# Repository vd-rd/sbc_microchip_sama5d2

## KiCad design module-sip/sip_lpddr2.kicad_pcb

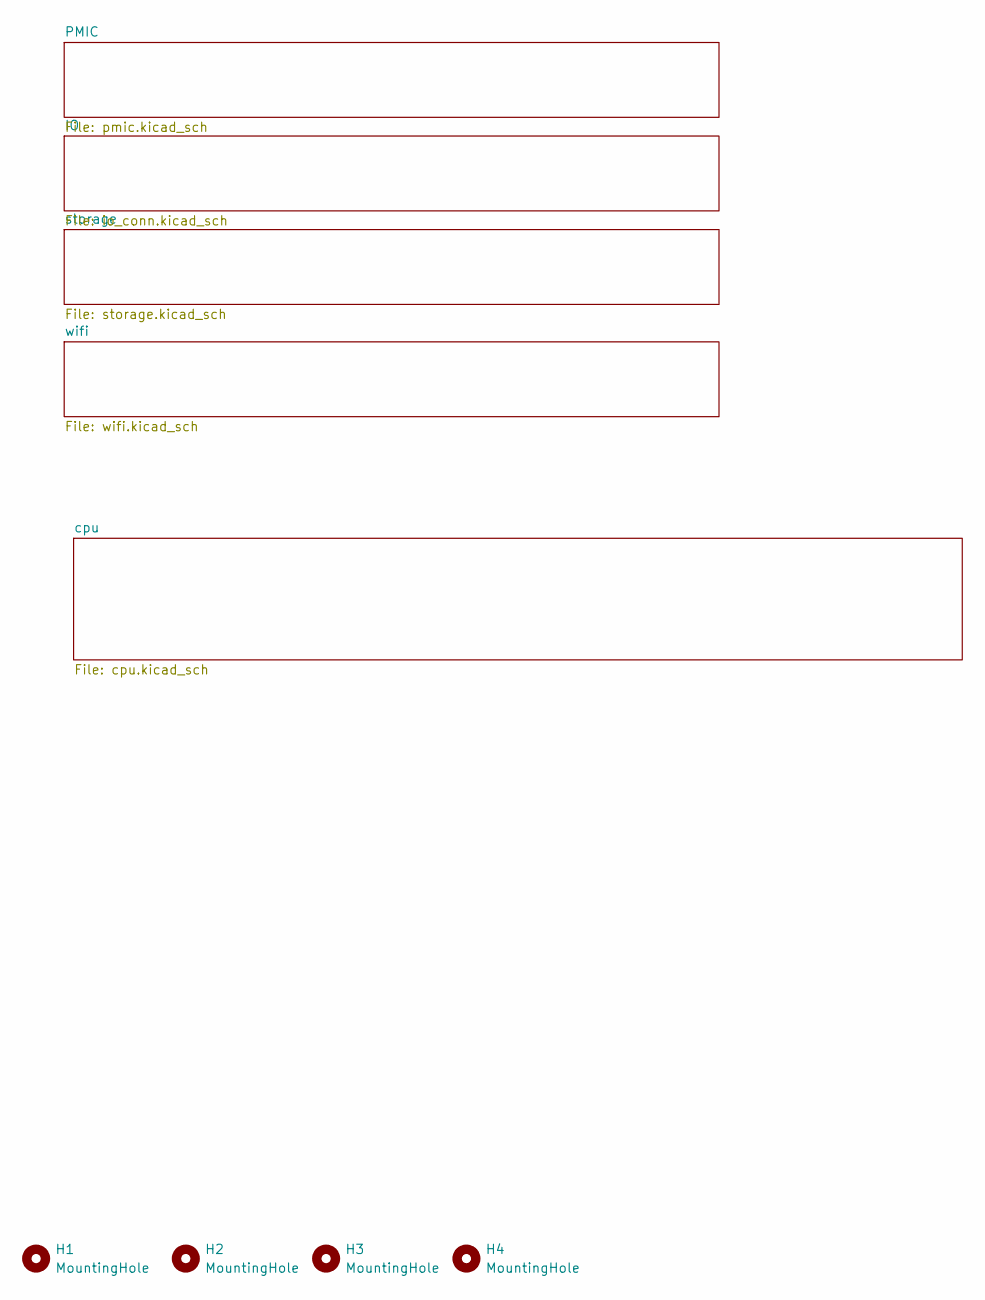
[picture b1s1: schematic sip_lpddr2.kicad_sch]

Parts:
H1, H2, H3, H4: MountingHole; MountingHole_2.7mm_M2.5

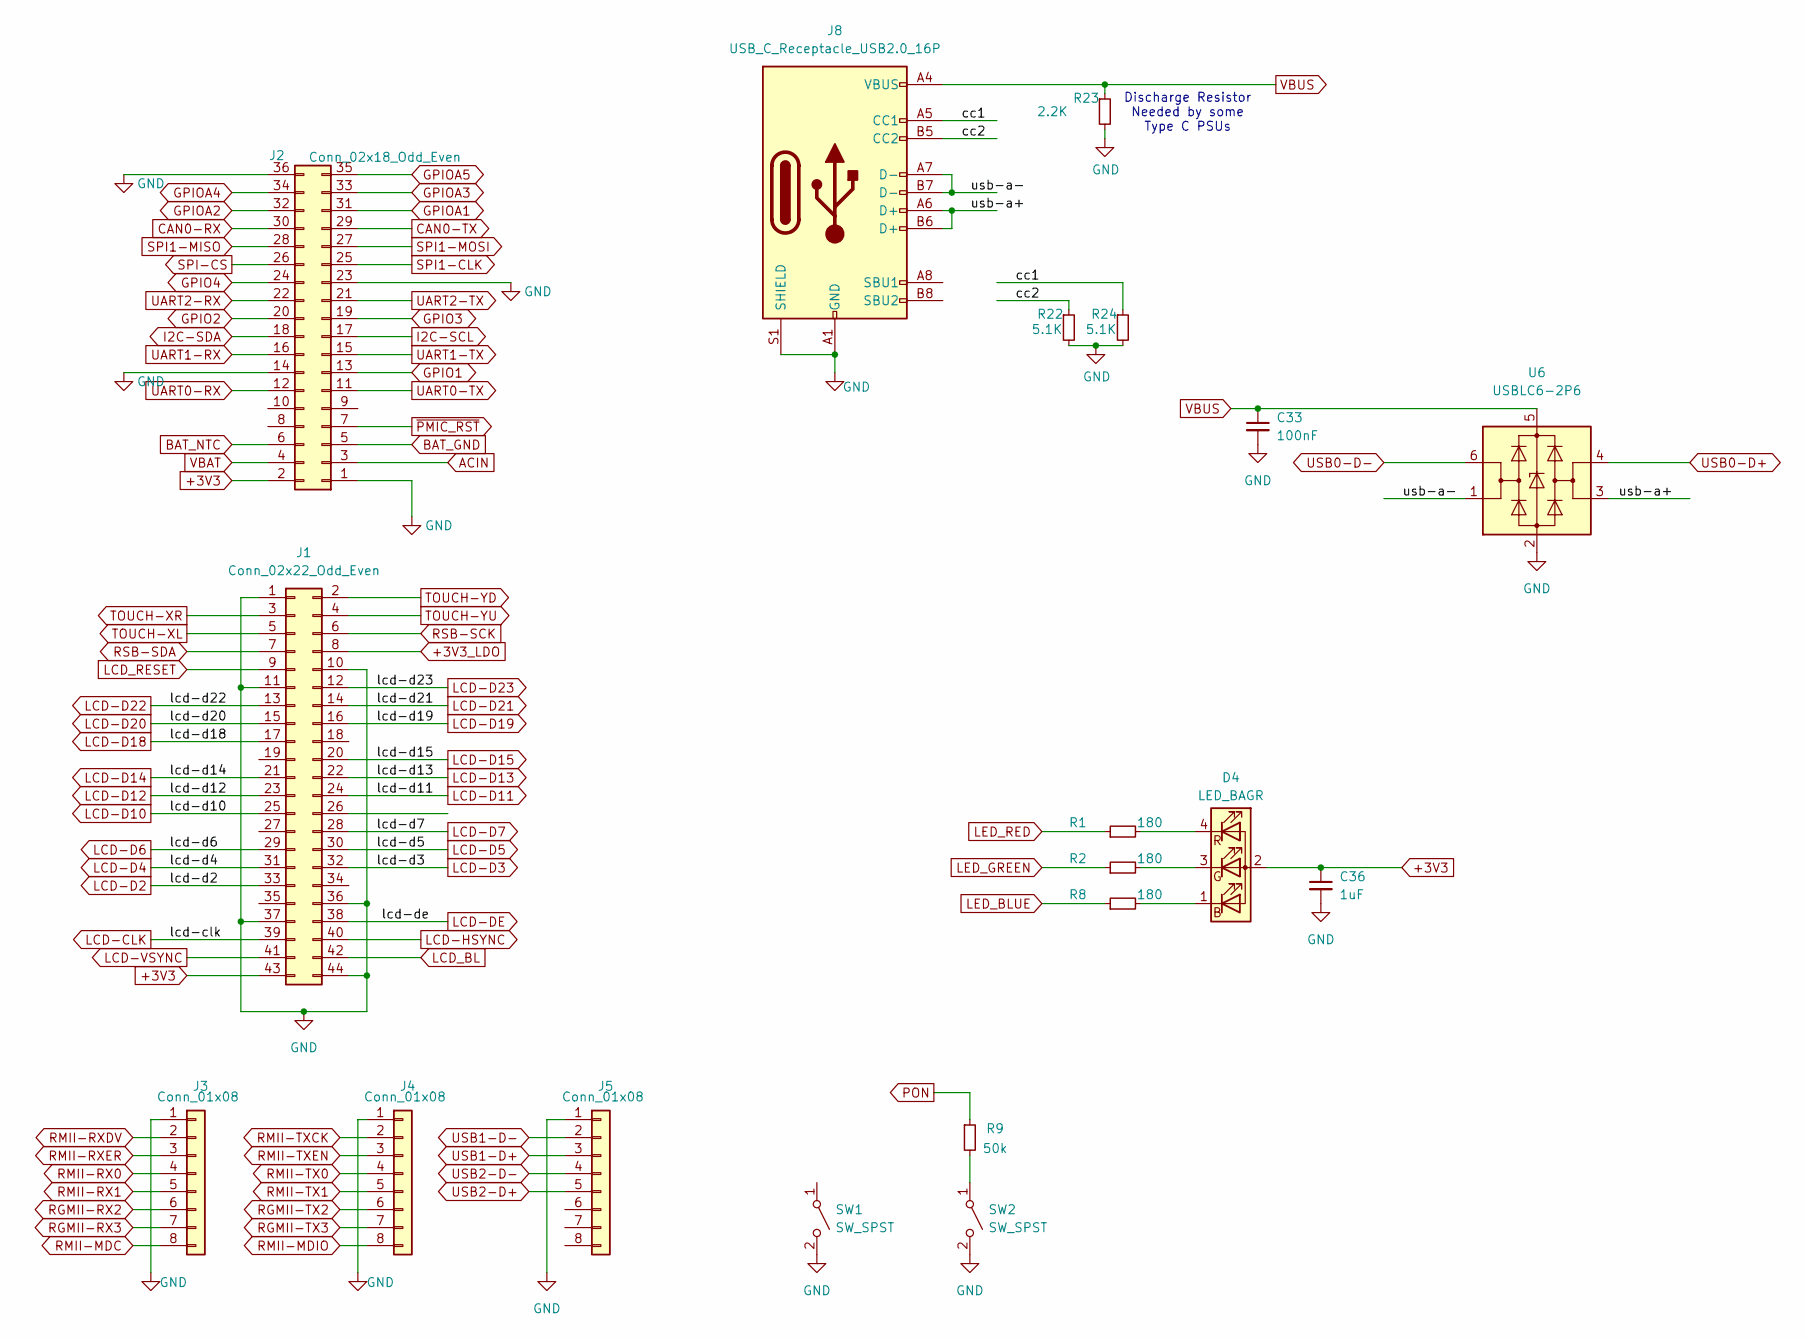
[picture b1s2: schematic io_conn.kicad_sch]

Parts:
C33: 100nF; C_0402_1005Metric
C36: 1uF; C_0402_1005Metric
D4: LED_BAGR; LED_RGB_Optosupply_OSTB0805C1E-A-0.8T
J1: Conn_02x22_Odd_Even; PinHeader_2x22_P1.27mm_Vertical
J2: Conn_02x18_Odd_Even; PinHeader_2x18_P2.54mm_Vertical
J3, J4, J5: Conn_01x08; PinHeader_2x04_P1.27mm_Vertical
J8: USB_C_Receptacle_USB2.0_16P; USB_C_Receptacle_GCT_USB4105-xx-A_16P_TopMnt_Horizontal
R1, R2, R8: 180; R_0402_1005Metric
R9: 50k; R_0402_1005Metric
R22, R24: 5.1K; R_0402_1005Metric; Part Description Resistor 2.2K M1005 1% 63mW
R23: 2.2K; R_0402_1005Metric; Part Description Resistor 2.2K M1005 1% 63mW
SW1, SW2: SW_SPST; SW_SPST_EVQP7C
U6: USBLC6-2P6; SOT-23-6

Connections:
+3V3: C36.1, D4.2 (A), J1.43, J2.2; also elsewhere on the board
+3V3_LDO: J1.8
/IO/cc1: J8.A5 (CC1), R24.1
/IO/cc2: J8.B5 (CC2), R22.1
/IO/usb-a+: J8.A6 (D+), J8.B6 (D+), U6.3 (I/O2)
/IO/usb-a-: J8.A7 (D-), J8.B7 (D-), U6.1 (I/O1)
ACIN: J2.3; also elsewhere on the board
BAT_GND: J2.5
BAT_NTC: J2.6; also elsewhere on the board
CAN0-RX: J2.30; also elsewhere on the board
CAN0-TX: J2.29; also elsewhere on the board
GND: C33.2, C36.2, J1.1, J1.10, J1.11, J1.36, J1.37, J1.44, J2.1, J2.14, J2.23, J2.36, J3.1, J4.1, J5.1, J8.A1 (GND), J8.A12 (GND), J8.B1 (GND), J8.B12 (GND), J8.S1 (SHIELD), R22.2, R23.2, R24.2, SW1.2 (B), SW2.2 (B), U6.2 (GND); also elsewhere on the board
GPIO1: J2.13
GPIO2: J2.20
GPIO3: J2.19
GPIO4: J2.24
GPIOA1: J2.31; also elsewhere on the board
GPIOA2: J2.32; also elsewhere on the board
GPIOA3: J2.33; also elsewhere on the board
GPIOA4: J2.34; also elsewhere on the board
GPIOA5: J2.35; also elsewhere on the board
I2C-SCL: J2.17; also elsewhere on the board
I2C-SDA: J2.18; also elsewhere on the board
LCD-CLK: J1.39; also elsewhere on the board
LCD-D2: J1.33; also elsewhere on the board
LCD-D3: J1.32; also elsewhere on the board
LCD-D4: J1.31; also elsewhere on the board
LCD-D5: J1.30; also elsewhere on the board
LCD-D6: J1.29; also elsewhere on the board
LCD-D7: J1.28; also elsewhere on the board
LCD-D10: J1.25; also elsewhere on the board
LCD-D11: J1.24; also elsewhere on the board
LCD-D12: J1.23; also elsewhere on the board
LCD-D13: J1.22; also elsewhere on the board
LCD-D14: J1.21; also elsewhere on the board
LCD-D15: J1.20; also elsewhere on the board
LCD-D18: J1.17; also elsewhere on the board
LCD-D19: J1.16; also elsewhere on the board
LCD-D20: J1.15; also elsewhere on the board
LCD-D21: J1.14; also elsewhere on the board
LCD-D22: J1.13; also elsewhere on the board
LCD-D23: J1.12; also elsewhere on the board
LCD-DE: J1.38; also elsewhere on the board
LCD-HSYNC: J1.40; also elsewhere on the board
LCD-VSYNC: J1.41; also elsewhere on the board
LCD_BL: J1.42
LCD_RESET: J1.9
LED_BLUE: R8.1
LED_GREEN: R2.1
LED_RED: R1.1
unnamed: D4.1 (BK), R8.2
unnamed: D4.3 (GK), R2.2
unnamed: D4.4 (RK), R1.2
unnamed: R9.2, SW2.1 (A)
PON: R9.1; also elsewhere on the board
RGMII-RX2: J3.6
RGMII-RX3: J3.7
RGMII-TX2: J4.6
RGMII-TX3: J4.7
RMII-MDC: J3.8; also elsewhere on the board
RMII-MDIO: J4.8; also elsewhere on the board
RMII-RX0: J3.4; also elsewhere on the board
RMII-RX1: J3.5; also elsewhere on the board
RMII-RXDV: J3.2; also elsewhere on the board
RMII-RXER: J3.3; also elsewhere on the board
RMII-TX0: J4.4; also elsewhere on the board
RMII-TX1: J4.5; also elsewhere on the board
RMII-TXCK: J4.2; also elsewhere on the board
RMII-TXEN: J4.3; also elsewhere on the board
RSB-SCK: J1.6
RSB-SDA: J1.7
SPI1-CLK: J2.25; also elsewhere on the board
SPI1-MISO: J2.28; also elsewhere on the board
SPI1-MOSI: J2.27; also elsewhere on the board
SPI-CS: J2.26; also elsewhere on the board
TOUCH-XL: J1.5
TOUCH-XR: J1.3
TOUCH-YD: J1.2
TOUCH-YU: J1.4
UART0-RX: J2.12; also elsewhere on the board
UART0-TX: J2.11; also elsewhere on the board
UART1-RX: J2.16; also elsewhere on the board
UART1-TX: J2.15; also elsewhere on the board
UART2-RX: J2.22
UART2-TX: J2.21
USB0-D+: U6.4 (I/O2); also elsewhere on the board
USB0-D-: U6.6 (I/O1); also elsewhere on the board
USB1-D+: J5.3; also elsewhere on the board
USB1-D-: J5.2; also elsewhere on the board
USB2-D+: J5.5
USB2-D-: J5.4
VBAT: J2.4; also elsewhere on the board
VBUS: C33.1, J8.A4 (VBUS), J8.A9 (VBUS), J8.B4 (VBUS), J8.B9 (VBUS), R23.1, U6.5 (VBUS); also elsewhere on the board
~PMIC_RST: J2.7; also elsewhere on the board

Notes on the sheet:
Discharge Resistor Needed by some Type C PSUs

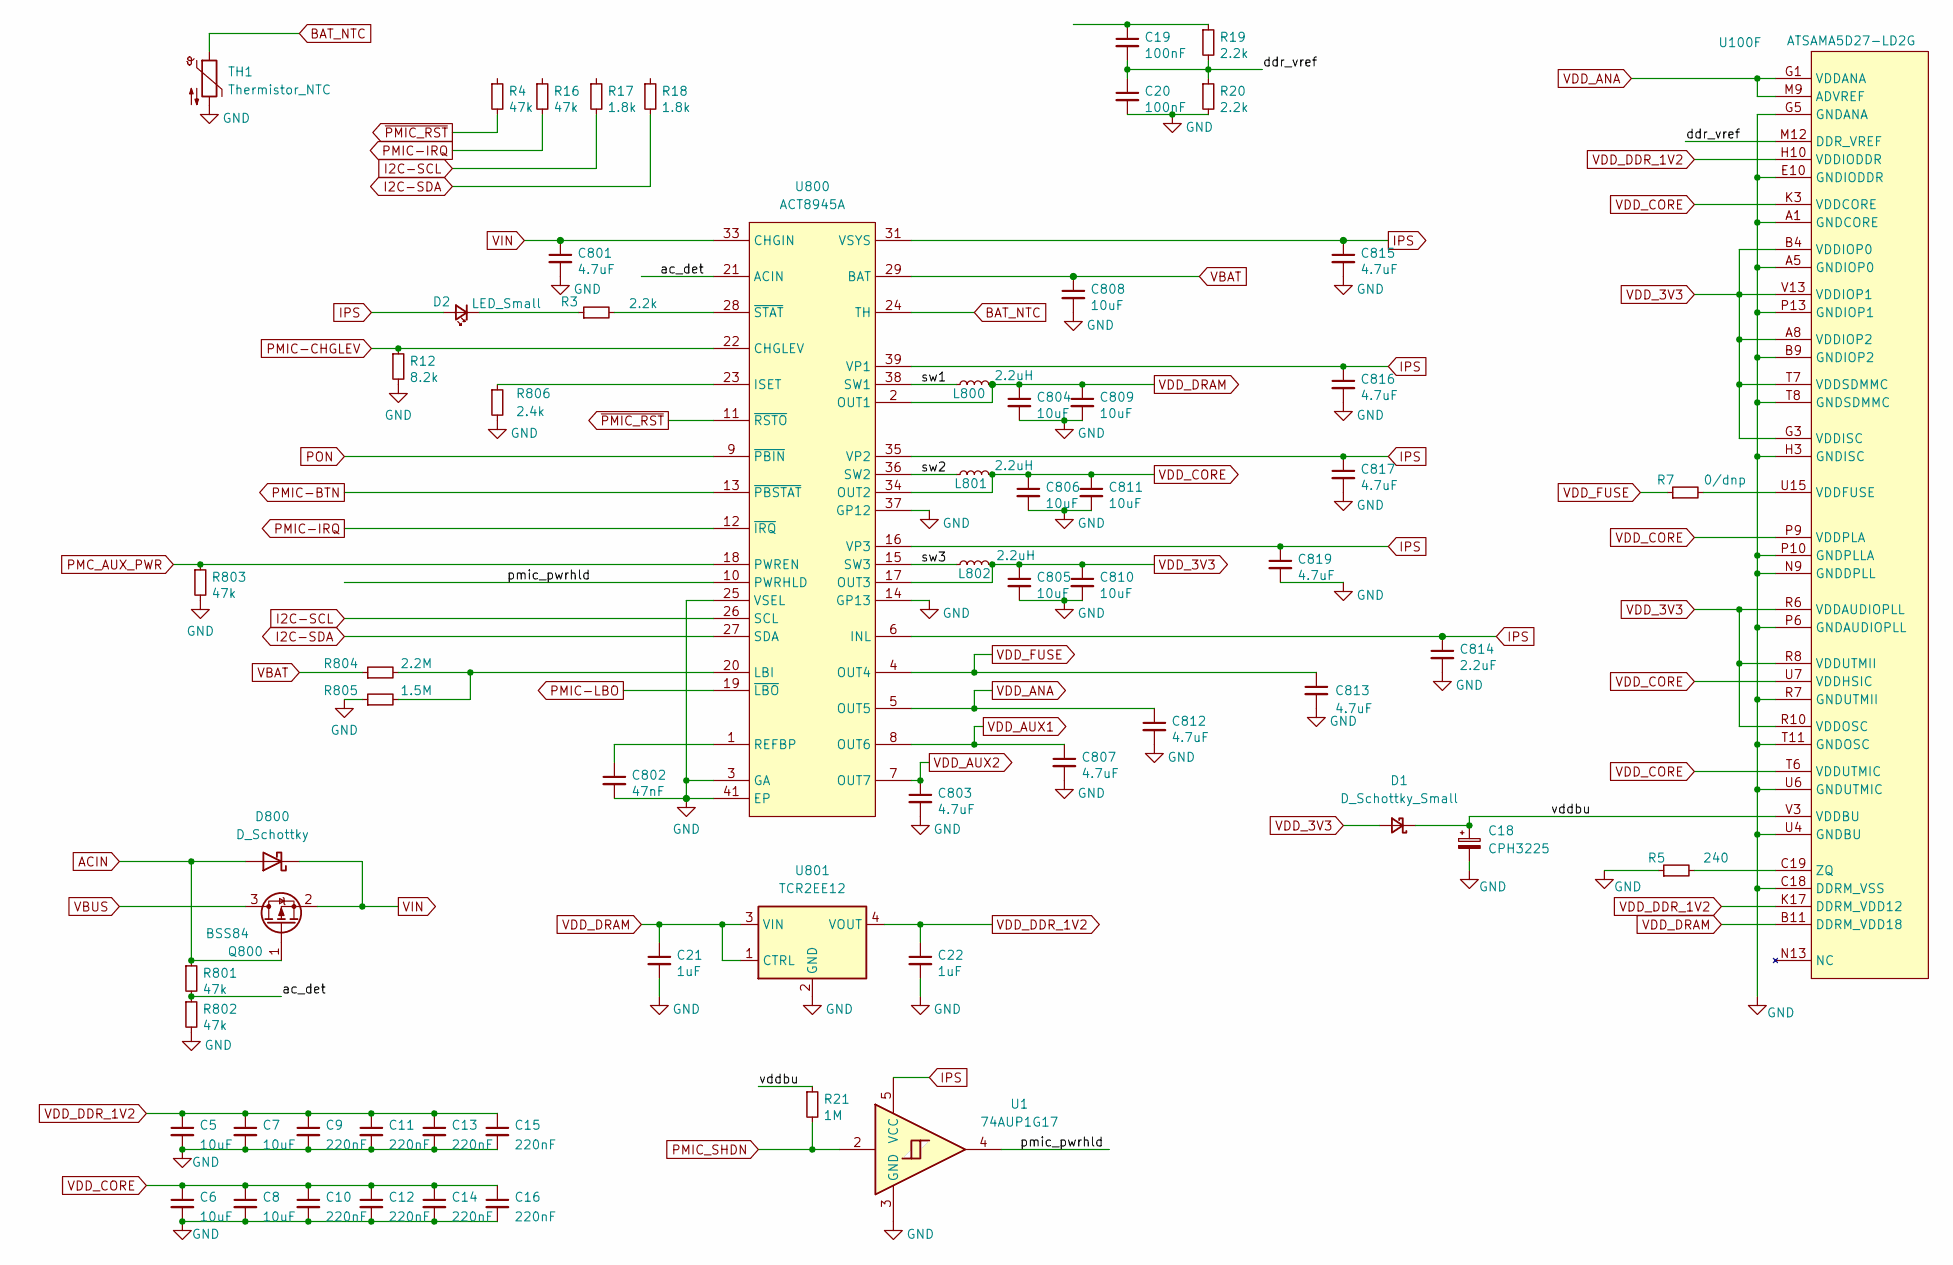
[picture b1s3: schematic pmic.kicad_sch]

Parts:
C5, C6, C7, C8, C804, C805, C806, C808, C809, C810, C811: 10uF; C_0603_1608Metric
C9, C10, C11, C12, C13, C14, C15, C16: 220nF; C_0402_1005Metric
C18: CPH3225; C_1210_3225Metric
C19, C20: 100nF; C_0402_1005Metric
C21, C22: 1uF; C_0402_1005Metric
C801, C803, C807, C812, C813, C815, C816, C817, C819: 4.7uF; C_0603_1608Metric
C802: 47nF; C_0402_1005Metric
C814: 2.2uF; C_0603_1608Metric
D1: D_Schottky_Small; D_SOD-323
D2: LED_Small; LED_0603_1608Metric
D800: D_Schottky; D_SOD-523
L800, L801, L802: 2.2uH; L_Wuerth_MAPI-2510
Q800: BSS84; SOT-323_SC-70
R3, R19, R20: 2.2k; R_0402_1005Metric
R4, R16, R801, R802, R803: 47k; R_0402_1005Metric
R5: 240; R_0402_1005Metric
R7: 0/dnp; R_0402_1005Metric
R12: 8.2k; R_0402_1005Metric
R17, R18: 1.8k; R_0402_1005Metric
R21: 1M; R_0402_1005Metric
R804: 2.2M; R_0402_1005Metric
R805: 1.5M; R_0402_1005Metric
R806: 2.4k; R_0402_1005Metric
TH1: Thermistor_NTC; R_0603_1608Metric
U1: 74AUP1G17; Texas_R-PDSO-N5_DRL-5
U100: ATSAMA5D27-LD2G; BGA361C80P19X19_1600X1600X120
U800: ACT8945A; TQFN-40-1EP_5x5mm_P0.4mm_EP3.5x3.5mm_ThermalVias
U801: TCR2EE12; SOT-553

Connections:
/PMIC/ac_det: R801.2, R802.1, U800.21 (ACIN)
/PMIC/ddr_vref: C19.2, C20.1, R19.2, R20.1, U100.J10 (DDR_VREF), U100.M12 (DDR_VREF)
/PMIC/pmic_pwrhld: U1.4, U800.10 (PWRHLD)
/PMIC/sw1: L800.1, U800.38 (SW1)
/PMIC/sw2: L801.1, U800.36 (SW2)
/PMIC/sw3: L802.1, U800.15 (SW3)
/PMIC/vddbu: C18.1, D1.1 (K), R21.1, U100.V3 (VDDBU)
ACIN: D800.2 (A), Q800.1 (G), R801.1; also elsewhere on the board
BAT_NTC: TH1.1, U800.24 (TH); also elsewhere on the board
GND: C5.2, C6.2, C7.2, C8.2, C9.2, C10.2, C11.2, C12.2, C13.2, C14.2, C15.2, C16.2, C18.2, C20.2, C21.2, C22.2, C801.2, C802.2, C803.2, C804.2, C805.2, C806.2, C807.2, C808.2, C809.2, C810.2, C811.2, C812.2, C813.2, C814.2, C815.2, C816.2, C817.2, C819.2, R5.1, R12.2, R20.2, R802.2, R803.2, R805.1, R806.2, TH1.2, U1.3 (GND), U100.A1 (GNDCORE), U100.A5 (GNDIOP0), U100.A14 (DDRM_VSS), U100.A19 (DDRM_VSS), U100.B9 (GNDIOP2), U100.B14 (DDRM_VSS), U100.B18 (DDRM_VSS), U100.C14 (DDRM_VSS), U100.C18 (DDRM_VSS), U100.D4 (GNDIOP0), U100.D9 (GNDCORE), U100.D14 (DDRM_VSS), U100.D18 (DDRM_VSS), U100.E10 (GNDIODDR), U100.E14 (DDRM_VSS), U100.E18 (DDRM_VSS), U100.F1 (GNDANA), U100.F8 (GNDIODDR), U100.F14 (DDRM_VSS), U100.F18 (DDRM_VSS), U100.G5 (GNDANA), U100.G10 (GNDIODDR), U100.G14 (DDRM_VSS), U100.G18 (DDRM_VSS), U100.H3 (GNDISC), U100.H14 (DDRM_VSS), U100.H18 (DDRM_VSS), U100.J9 (GNDIODDR), U100.J11 (GNDCORE), U100.K4 (GNDCORE), U100.K7 (GNDCORE), U100.L11 (GNDIODDR), U100.M13 (GNDIODDR), U100.N9 (GNDDPLL), U100.N12 (GNDIODDR), U100.N14 (DDRM_VSS), U100.N17 (DDRM_VSS), U100.N18 (DDRM_VSS), U100.P6 (GNDAUDIOPLL), U100.P10 (GNDPLLA), U100.P13 (GNDIOP1), U100.P14 (DDRM_VSS), U100.P18 (DDRM_VSS), U100.R7 (GNDUTMII), U100.R13 (GNDIOP1), U100.R14 (DDRM_VSS), U100.R18 (DDRM_VSS), U100.T8 (GNDSDMMC), U100.T11 (GNDOSC), U100.T18 (DDRM_VSS), U100.U4 (GNDBU), U100.U6 (GNDUTMIC), U100.V9 (GNDCORE), U100.W1 (GNDCORE), U100.W13 (GNDIOP1), U100.W19 (GNDIOP1), U800.3 (GA), U800.14 (GP13), U800.25 (VSEL), U800.37 (GP12), U800.41 (EP), U801.2 (GND); also elsewhere on the board
I2C-SCL: R17.2, U800.26 (SCL); also elsewhere on the board
I2C-SDA: R18.2, U800.27 (SDA); also elsewhere on the board
IPS: C814.1, C815.1, C816.1, C817.1, C819.1, D2.2 (A), U1.5 (VCC), U800.6 (INL), U800.16 (VP3), U800.31 (VSYS), U800.32 (VSYS), U800.35 (VP2), U800.39 (VP1)
unnamed: C19.1, R19.1
unnamed: D2.1 (K), R3.1
unnamed: R7.2, U100.U15 (VDDFUSE)
unnamed: R5.2, U100.C19 (ZQ)
unnamed: R806.1, U800.23 (ISET)
unnamed: R804.2, R805.2, U800.20 (LBI)
unnamed: C802.1, U800.1 (REFBP)
unnamed: R3.2, U800.28 (~STAT)
PMC_AUX_PWR: R803.1, U800.18 (PWREN)
PMIC-BTN: U800.13 (~PBSTAT); also elsewhere on the board
PMIC-CHGLEV: R12.1, U800.22 (CHGLEV)
PMIC-IRQ: R16.2, U800.12 (~IRQ); also elsewhere on the board
PMIC-LBO: U800.19 (~LBO)
PMIC_SHDN: R21.2, U1.2; also elsewhere on the board
PON: U800.9 (~PBIN); also elsewhere on the board
VBAT: C808.1, R804.1, U800.29 (BAT), U800.30 (BAT); also elsewhere on the board
VBUS: Q800.3 (D); also elsewhere on the board
VDD_3V3: C805.1, C810.1, D1.2 (A), L802.2, U100.A8 (VDDIOP2), U100.B4 (VDDIOP0), U100.D5 (VDDIOP0), U100.G3 (VDDISC), U100.R6 (VDDAUDIOPLL), U100.R8 (VDDUTMII), U100.R10 (VDDOSC), U100.T7 (VDDSDMMC), U100.V13 (VDDIOP1), U100.V18 (VDDIOP1), U800.17 (OUT3)
VDD_ANA: C812.1, U100.G1 (VDDANA), U100.H6 (VDDANA), U100.M9 (ADVREF), U800.5 (OUT5)
VDD_AUX1: C807.1, U800.8 (OUT6)
VDD_AUX2: C803.1, U800.7 (OUT7)
VDD_CORE: C6.1, C8.1, C10.1, C12.1, C14.1, C16.1, C806.1, C811.1, L801.2, U100.C3 (VDDCORE), U100.C9 (VDDCORE), U100.K3 (VDDCORE), U100.K8 (VDDCORE), U100.P9 (VDDPLA), U100.T6 (VDDUTMIC), U100.U7 (VDDHSIC), U100.U9 (VDDCORE), U100.V5 (VDDCORE), U100.W6 (VDDCORE), U800.34 (OUT2)
VDD_DDR_1V2: C5.1, C7.1, C9.1, C11.1, C13.1, C15.1, C22.1, U100.B15 (DDRM_VDD12), U100.B17 (DDRM_VDD12), U100.B19 (DDRM_VDD12), U100.D15 (DDRM_VDD12), U100.D17 (DDRM_VDD12), U100.D19 (DDRM_VDD12), U100.E8 (VDDIODDR), U100.E11 (VDDIODDR), U100.F15 (DDRM_VDD12), U100.F17 (DDRM_VDD12), U100.F19 (DDRM_VDD12), U100.H10 (VDDIODDR), U100.H15 (DDRM_VDD12), U100.H17 (DDRM_VDD12), U100.H19 (DDRM_VDD12), U100.J8 (VDDIODDR), U100.J13 (VDDIODDR), U100.K15 (DDRM_VDD12), U100.K17 (DDRM_VDD12), U100.K19 (DDRM_VDD12), U100.L10 (VDDIODDR), U100.M15 (DDRM_VDD12), U100.M17 (DDRM_VDD12), U100.M19 (DDRM_VDD12), U100.P12 (VDDIODDR), U100.P15 (DDRM_VDD12), U100.P17 (DDRM_VDD12), U100.P19 (DDRM_VDD12), U100.T17 (DDRM_VDD12), U100.T19 (DDRM_VDD12), U801.4 (VOUT)
VDD_DRAM: C21.1, C804.1, C809.1, L800.2, U100.B11 (DDRM_VDD18), U100.B13 (DDRM_VDD18), U100.D11 (DDRM_VDD18), U100.D13 (DDRM_VDD18), U100.K13 (DDRM_VDD18), U100.K16 (DDRM_VDD18), U800.2 (OUT1), U801.1 (CTRL), U801.3 (VIN)
VDD_FUSE: C813.1, R7.1, U800.4 (OUT4)
VIN: C801.1, D800.1 (K), Q800.2 (S), U800.33 (CHGIN)
~PMIC_RST: R4.2, U800.11 (~RSTO); also elsewhere on the board

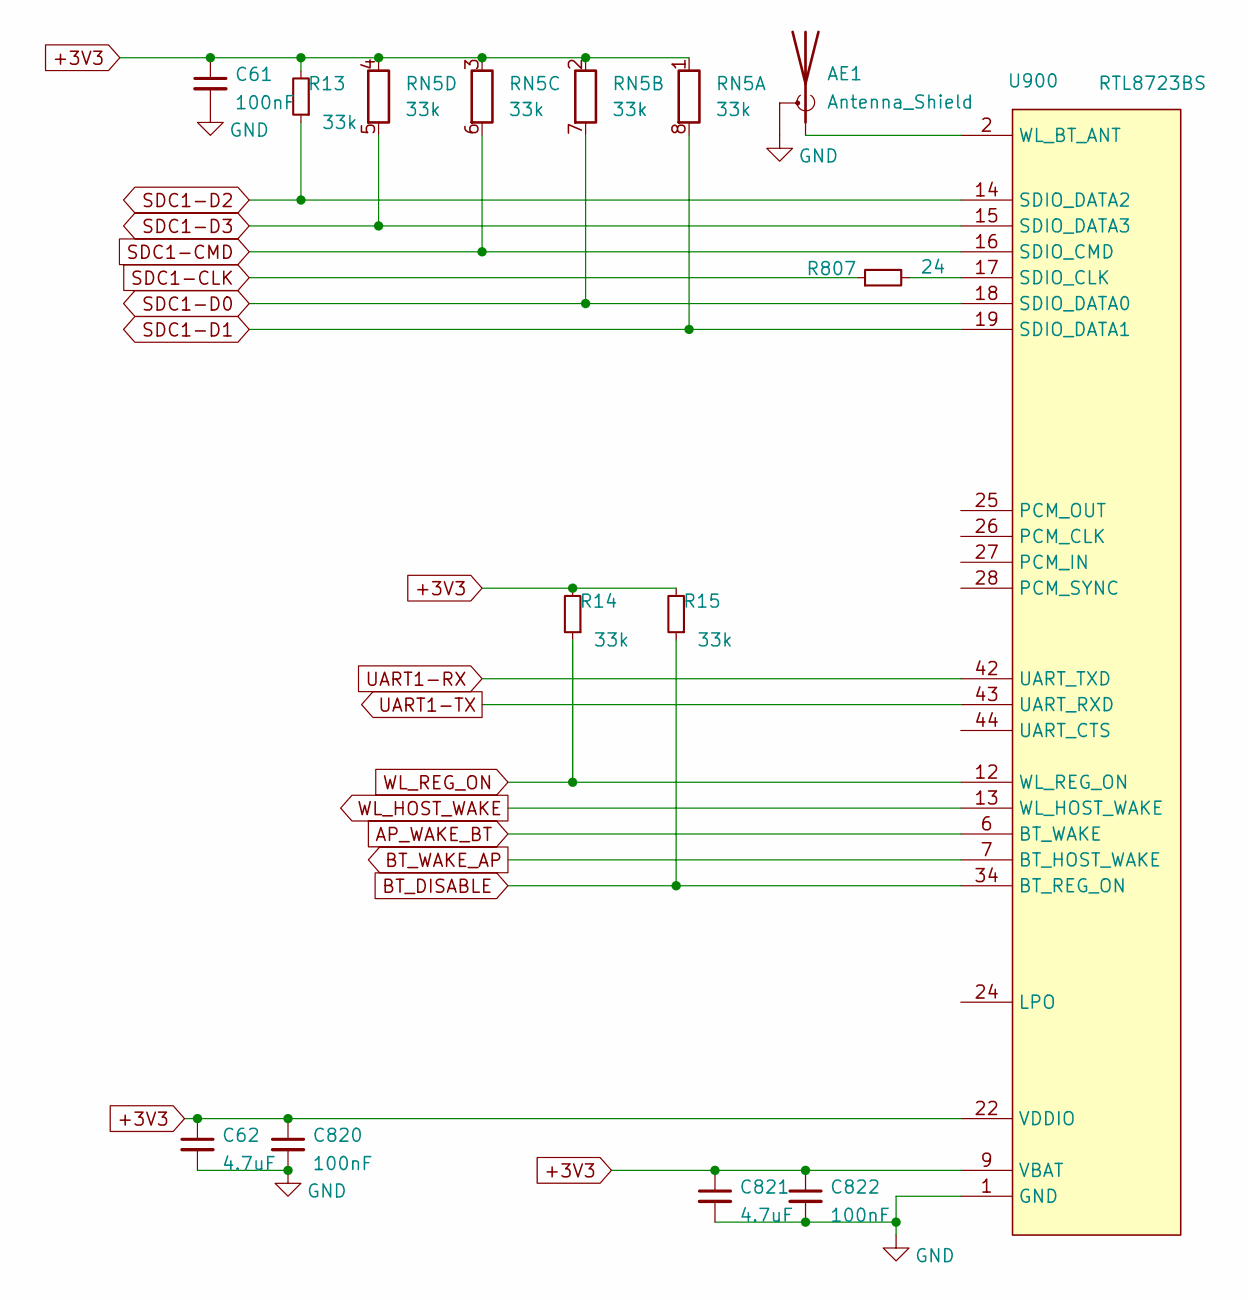
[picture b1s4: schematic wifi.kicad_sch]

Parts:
AE1: Antenna_Shield; U.FL_Hirose_U.FL-R-SMT-1_Vertical
C61, C820, C822: 100nF; C_0402_1005Metric
C62, C821: 4.7uF; C_0603_1608Metric
R13, R14, R15: 33k; R_0402_1005Metric
R807: 24; R_0402_1005Metric
RN5: 33k; R_Array_Concave_4x0402
U900: RTL8723BS; lga44_12x12mm_P0.9

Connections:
+3V3: C61.1, C62.1, C820.1, C821.1, C822.1, R13.2, R14.2, R15.2, RN5.1 (R1.1), RN5.2 (R2.1), RN5.3 (R3.1), RN5.4 (R4.1), U900.9 (VBAT), U900.22 (VDDIO); also elsewhere on the board
AP_WAKE_BT: U900.6 (BT_WAKE)
BT_DISABLE: R15.1, U900.34 (BT_REG_ON)
BT_WAKE_AP: U900.7 (BT_HOST_WAKE)
GND: AE1.2 (Shield), C61.2, C62.2, C820.2, C821.2, C822.2, U900.1 (GND), U900.3 (GND), U900.20 (GND), U900.31 (GND), U900.33 (GND), U900.36 (GND), U900.41 (GND); also elsewhere on the board
unnamed: AE1.1 (A), U900.2 (WL_BT_ANT)
unnamed: R807.2, U900.17 (SDIO_CLK)
SDC1-CLK: R807.1
SDC1-CMD: RN5.6 (R3.2), U900.16 (SDIO_CMD)
SDC1-D0: RN5.7 (R2.2), U900.18 (SDIO_DATA0)
SDC1-D1: RN5.8 (R1.2), U900.19 (SDIO_DATA1)
SDC1-D2: R13.1, U900.14 (SDIO_DATA2)
SDC1-D3: RN5.5 (R4.2), U900.15 (SDIO_DATA3)
UART1-RX: U900.42 (UART_TXD); also elsewhere on the board
UART1-TX: U900.43 (UART_RXD); also elsewhere on the board
WL_HOST_WAKE: U900.13 (WL_HOST_WAKE)
WL_REG_ON: R14.1, U900.12 (WL_REG_ON)

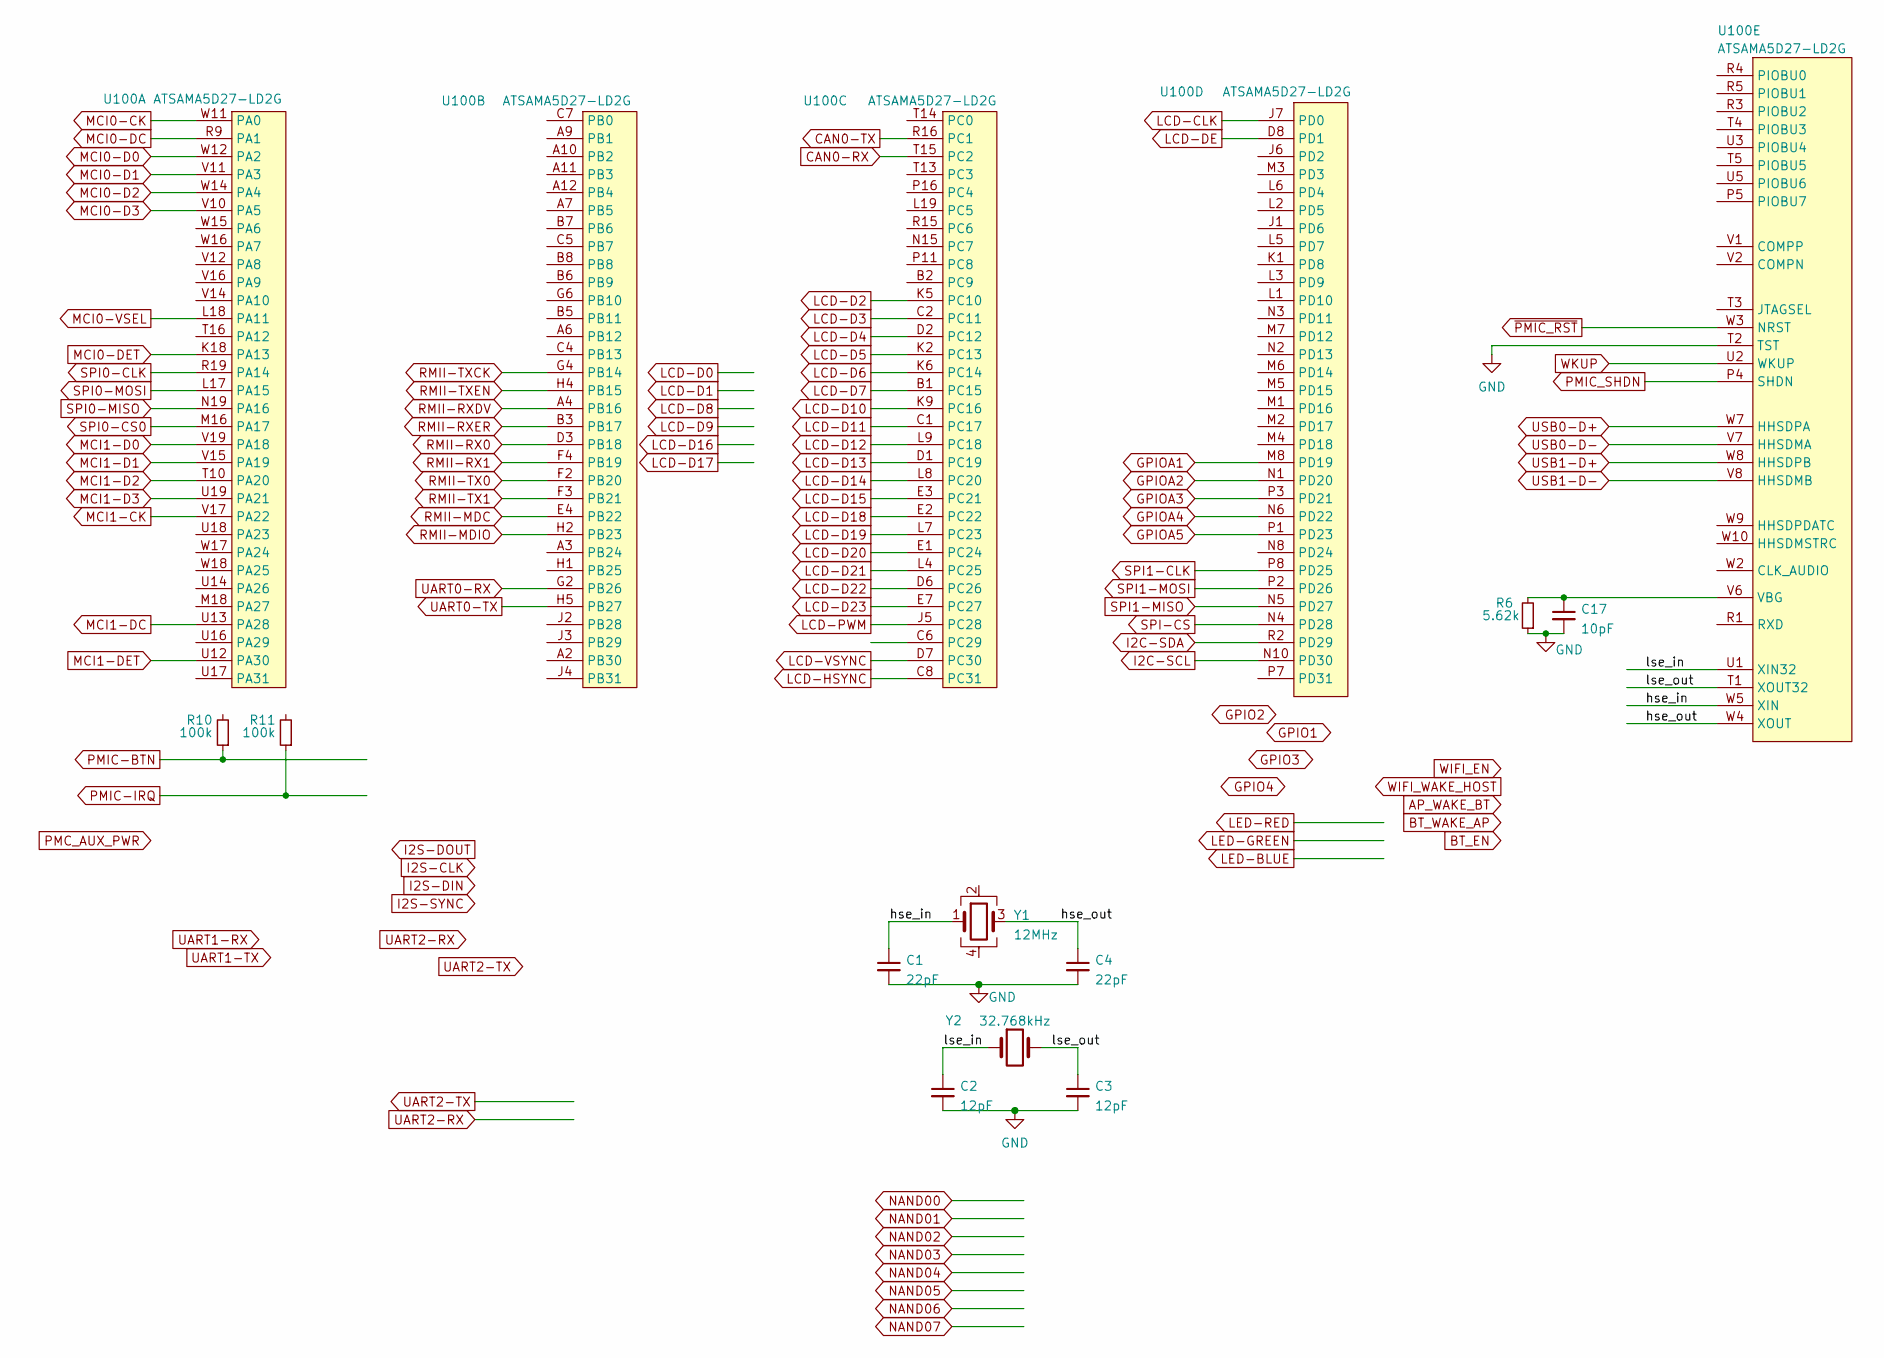
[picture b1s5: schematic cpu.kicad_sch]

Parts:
C1, C4: 22pF; C_0402_1005Metric
C2, C3: 12pF; C_0402_1005Metric
C17: 10pF; C_0402_1005Metric
R6: 5.62k; R_0402_1005Metric
R10, R11: 100k; R_0402_1005Metric
U100: ATSAMA5D27-LD2G; BGA361C80P19X19_1600X1600X120
Y1: 12MHz; Crystal_SMD_3225-4Pin_3.2x2.5mm
Y2: 32.768kHz; Crystal_SMD_3215-2Pin_3.2x1.5mm

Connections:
/cpu/hse_in: C1.1, U100.W5 (XIN), Y1.1
/cpu/hse_out: C4.1, U100.W4 (XOUT), Y1.3
/cpu/lse_in: C2.1, U100.U1 (XIN32), Y2.1
/cpu/lse_out: C3.1, U100.T1 (XOUT32), Y2.2
CAN0-RX: U100.T15 (PC2); also elsewhere on the board
CAN0-TX: U100.R16 (PC1); also elsewhere on the board
GND: C1.2, C2.2, C3.2, C4.2, C17.2, R6.1, U100.T2 (TST); also elsewhere on the board
GPIOA1: U100.M8 (PD19); also elsewhere on the board
GPIOA2: U100.N1 (PD20); also elsewhere on the board
GPIOA3: U100.P3 (PD21); also elsewhere on the board
GPIOA4: U100.N6 (PD22); also elsewhere on the board
GPIOA5: U100.P1 (PD23); also elsewhere on the board
I2C-SCL: U100.N10 (PD30); also elsewhere on the board
I2C-SDA: U100.R2 (PD29); also elsewhere on the board
LCD-CLK: U100.J7 (PD0); also elsewhere on the board
LCD-D2: U100.K5 (PC10); also elsewhere on the board
LCD-D3: U100.C2 (PC11); also elsewhere on the board
LCD-D4: U100.D2 (PC12); also elsewhere on the board
LCD-D5: U100.K2 (PC13); also elsewhere on the board
LCD-D6: U100.K6 (PC14); also elsewhere on the board
LCD-D7: U100.B1 (PC15); also elsewhere on the board
LCD-D10: U100.K9 (PC16); also elsewhere on the board
LCD-D11: U100.C1 (PC17); also elsewhere on the board
LCD-D12: U100.L9 (PC18); also elsewhere on the board
LCD-D13: U100.D1 (PC19); also elsewhere on the board
LCD-D14: U100.L8 (PC20); also elsewhere on the board
LCD-D15: U100.E3 (PC21); also elsewhere on the board
LCD-D18: U100.E2 (PC22); also elsewhere on the board
LCD-D19: U100.L7 (PC23); also elsewhere on the board
LCD-D20: U100.E1 (PC24); also elsewhere on the board
LCD-D21: U100.L4 (PC25); also elsewhere on the board
LCD-D22: U100.D6 (PC26); also elsewhere on the board
LCD-D23: U100.E7 (PC27); also elsewhere on the board
LCD-DE: U100.D8 (PD1); also elsewhere on the board
LCD-HSYNC: U100.C8 (PC31); also elsewhere on the board
LCD-PWM: U100.J5 (PC28)
LCD-VSYNC: U100.D7 (PC30); also elsewhere on the board
MCI0-CK: U100.W11 (PA0); also elsewhere on the board
MCI0-D0: U100.W12 (PA2); also elsewhere on the board
MCI0-D1: U100.V11 (PA3); also elsewhere on the board
MCI0-D2: U100.W14 (PA4); also elsewhere on the board
MCI0-D3: U100.V10 (PA5); also elsewhere on the board
MCI0-DC: U100.R9 (PA1); also elsewhere on the board
MCI0-DET: U100.K18 (PA13); also elsewhere on the board
MCI0-VSEL: U100.L18 (PA11)
MCI1-CK: U100.V17 (PA22)
MCI1-D0: U100.V19 (PA18)
MCI1-D1: U100.V15 (PA19)
MCI1-D2: U100.T10 (PA20)
MCI1-D3: U100.U19 (PA21)
MCI1-DC: U100.U13 (PA28)
MCI1-DET: U100.U12 (PA30)
unnamed: C17.1, R6.2, U100.V6 (VBG)
PMIC-BTN: R10.1; also elsewhere on the board
PMIC-IRQ: R11.1; also elsewhere on the board
PMIC_SHDN: U100.P4 (SHDN); also elsewhere on the board
RMII-MDC: U100.E4 (PB22); also elsewhere on the board
RMII-MDIO: U100.H2 (PB23); also elsewhere on the board
RMII-RX0: U100.D3 (PB18); also elsewhere on the board
RMII-RX1: U100.F4 (PB19); also elsewhere on the board
RMII-RXDV: U100.A4 (PB16); also elsewhere on the board
RMII-RXER: U100.B3 (PB17); also elsewhere on the board
RMII-TX0: U100.F2 (PB20); also elsewhere on the board
RMII-TX1: U100.F3 (PB21); also elsewhere on the board
RMII-TXCK: U100.G4 (PB14); also elsewhere on the board
RMII-TXEN: U100.H4 (PB15); also elsewhere on the board
SPI0-CLK: U100.R19 (PA14)
SPI0-CS0: U100.M16 (PA17)
SPI0-MISO: U100.N19 (PA16)
SPI0-MOSI: U100.L17 (PA15)
SPI1-CLK: U100.P8 (PD25); also elsewhere on the board
SPI1-MISO: U100.N5 (PD27); also elsewhere on the board
SPI1-MOSI: U100.P2 (PD26); also elsewhere on the board
SPI-CS: U100.N4 (PD28); also elsewhere on the board
UART0-RX: U100.G2 (PB26); also elsewhere on the board
UART0-TX: U100.H5 (PB27); also elsewhere on the board
USB0-D+: U100.W7 (HHSDPA); also elsewhere on the board
USB0-D-: U100.V7 (HHSDMA); also elsewhere on the board
USB1-D+: U100.W8 (HHSDPB); also elsewhere on the board
USB1-D-: U100.V8 (HHSDMB); also elsewhere on the board
WKUP: U100.U2 (WKUP)
~PMIC_RST: U100.W3 (NRST); also elsewhere on the board

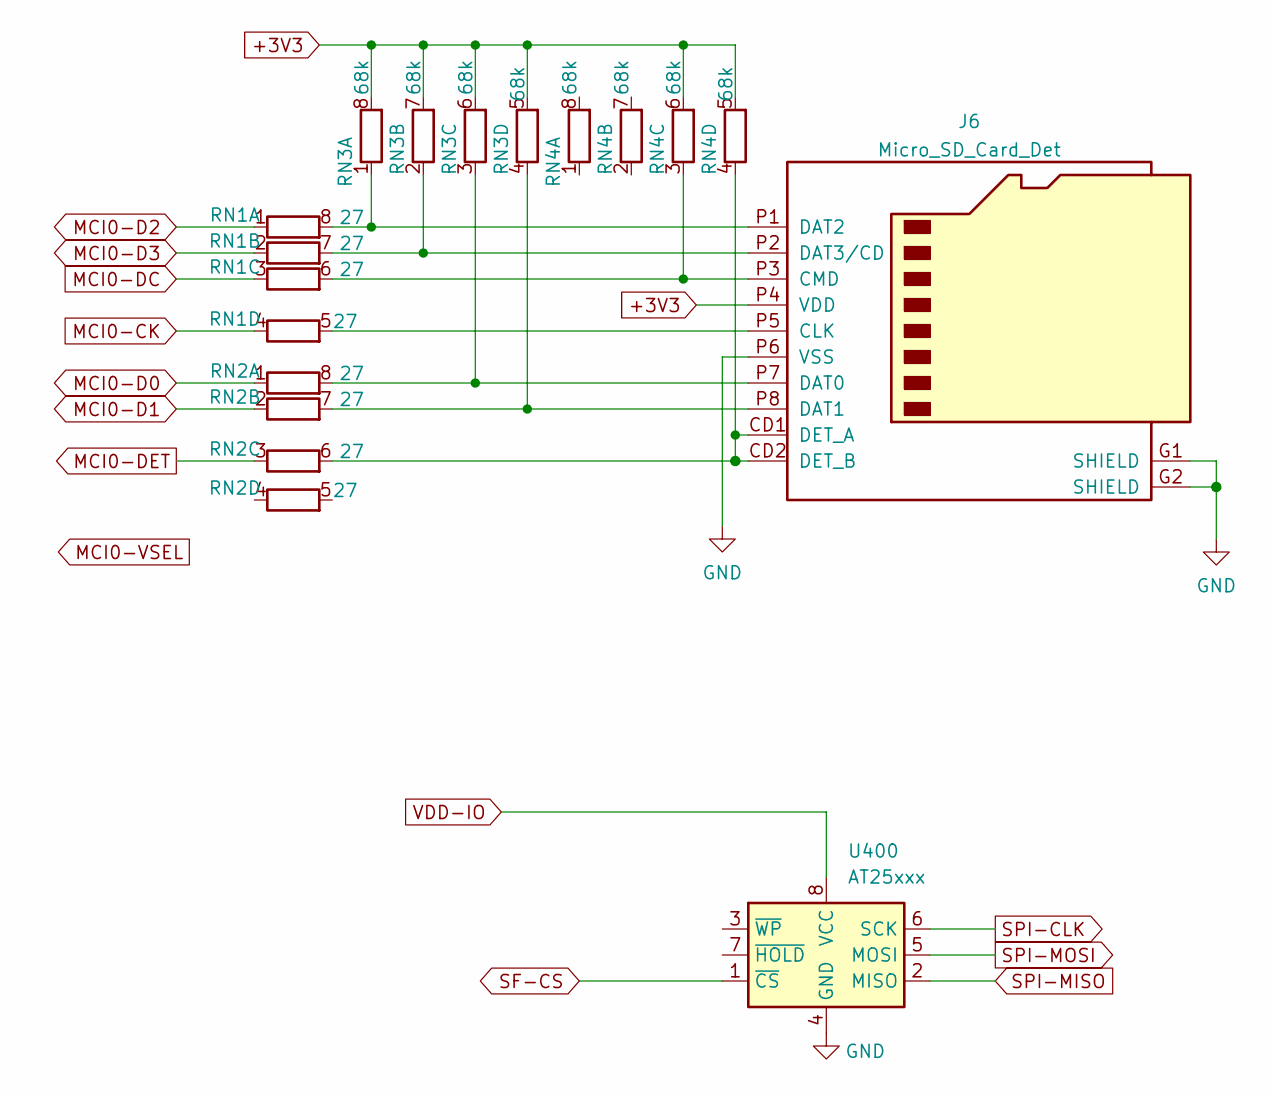
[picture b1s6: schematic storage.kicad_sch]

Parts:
J6: Micro_SD_Card_Det; MEM20610118800A
RN1, RN2: 27; R_Array_Concave_4x0402
RN3, RN4: 68k; R_Array_Concave_4x0402
U400: AT25xxx; SOIC-8_3.9x4.9mm_P1.27mm

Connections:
+3V3: J6.P4 (VDD), RN3.5 (R4.2), RN3.6 (R3.2), RN3.7 (R2.2), RN3.8 (R1.2), RN4.5 (R4.2), RN4.6 (R3.2); also elsewhere on the board
GND: J6.G1 (SHIELD), J6.G2 (SHIELD), J6.P6 (VSS), U400.4 (GND); also elsewhere on the board
MCI0-CK: RN1.4 (R4.1); also elsewhere on the board
MCI0-D0: RN2.1 (R1.1); also elsewhere on the board
MCI0-D1: RN2.2 (R2.1); also elsewhere on the board
MCI0-D2: RN1.1 (R1.1); also elsewhere on the board
MCI0-D3: RN1.2 (R2.1); also elsewhere on the board
MCI0-DC: RN1.3 (R3.1); also elsewhere on the board
MCI0-DET: RN2.3 (R3.1); also elsewhere on the board
unnamed: J6.P5 (CLK), RN1.5 (R4.2)
unnamed: J6.P3 (CMD), RN1.6 (R3.2), RN4.3 (R3.1)
unnamed: J6.P7 (DAT0), RN2.8 (R1.2), RN3.3 (R3.1)
unnamed: J6.P8 (DAT1), RN2.7 (R2.2), RN3.4 (R4.1)
unnamed: J6.P1 (DAT2), RN1.8 (R1.2), RN3.1 (R1.1)
unnamed: J6.P2 (DAT3/CD), RN1.7 (R2.2), RN3.2 (R2.1)
unnamed: J6.CD1 (DET_A), J6.CD2 (DET_B), RN2.6 (R3.2), RN4.4 (R4.1)
SF-CS: U400.1 (~CS)
SPI-CLK: U400.6 (SCK)
SPI-MISO: U400.2 (MISO)
SPI-MOSI: U400.5 (MOSI)
VDD-IO: U400.8 (VCC)
